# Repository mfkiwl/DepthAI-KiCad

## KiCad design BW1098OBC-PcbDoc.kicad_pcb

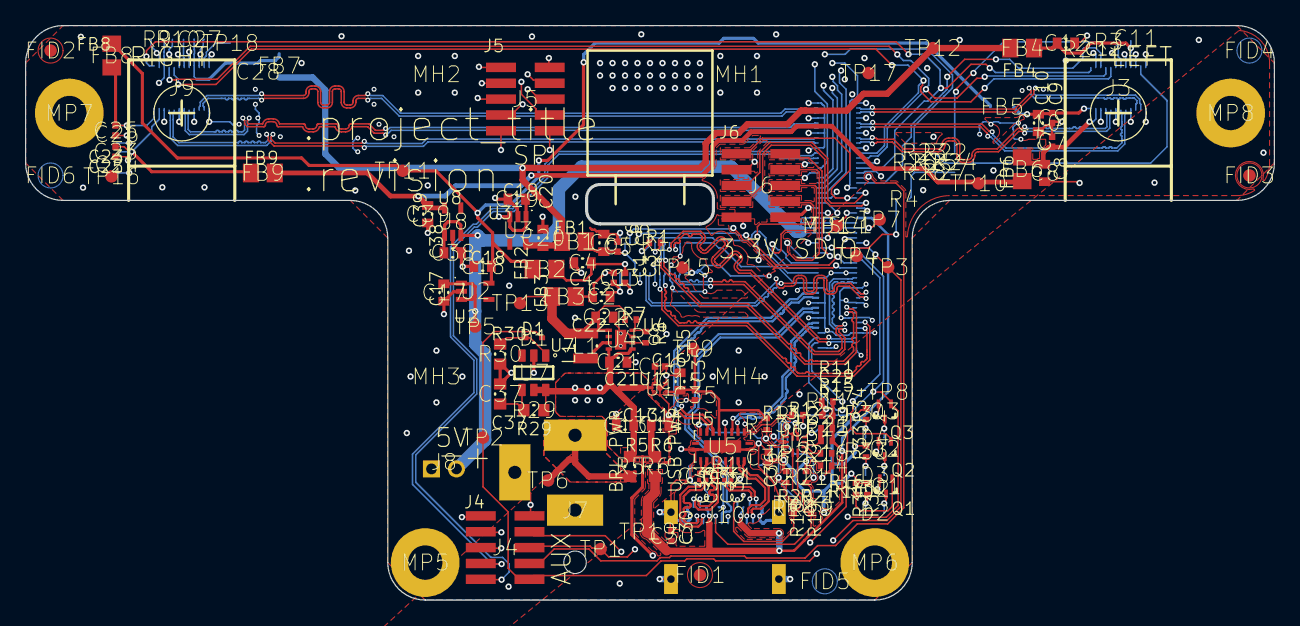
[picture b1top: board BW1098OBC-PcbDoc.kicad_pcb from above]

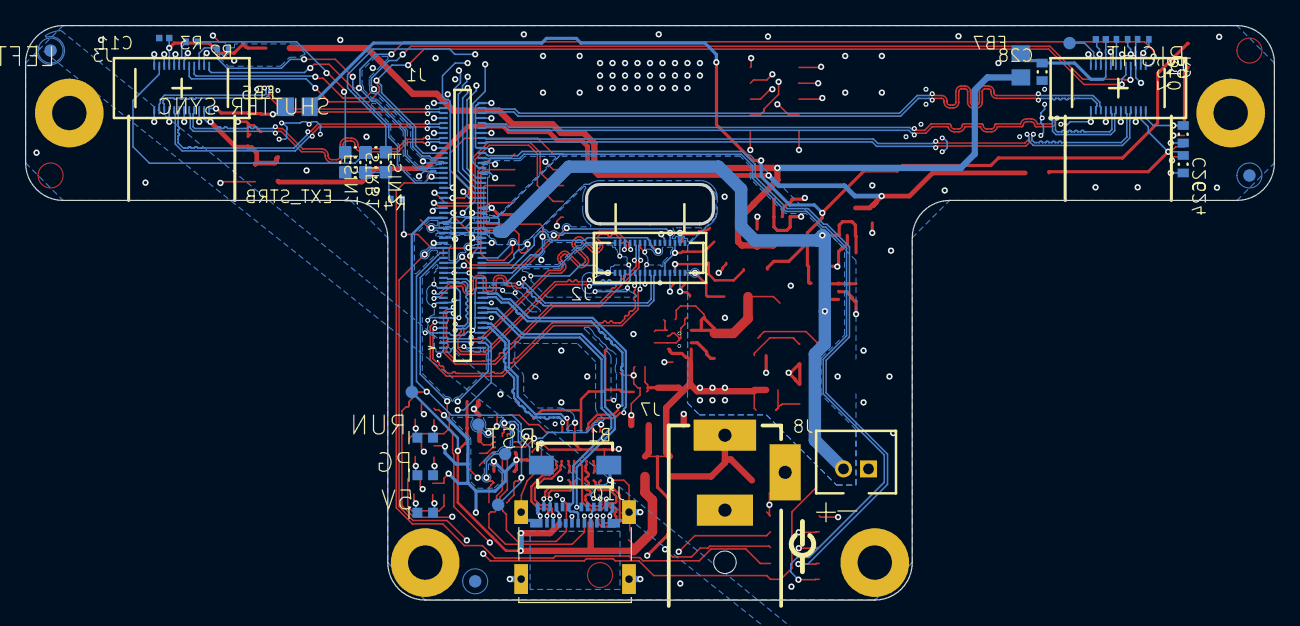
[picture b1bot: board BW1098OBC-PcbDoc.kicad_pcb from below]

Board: 4 copper layers, 100.0 x 46.0 mm, 146 parts (43 on the bottom side), 118 nets.

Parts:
B1: B1; DTSM-32N-V
C1: C1; CAPC0402(1005)70_L
C2: C2; CAPC0603(1608)100_L
C3: C3; CAPC0402(1005)70_L
C4: C4; CAPC0603(1608)100_L
C5: C5; CAPC0402(1005)70_L
C6: C6; CAPC0603(1608)100_L
C7: C7; CAPC0402(1005)70_L
C8: C8; CAPC0603(1608)100_L
C9: C9; CAPC0402(1005)70_L
C10: C10; CAPC0603(1608)100_L
C11: C11; CAPC0402(1005)70_L
C12: C12; CAPC0603(1608)100_L
C13: C13; CAPC0603(1608)100_L
C14: C14; CAPC0603(1608)100_L
C15: C15; CAPC0603(1608)100_L
C16: C16; CAPC0402(1005)70_L
C17: C17; CAPC0603(1608)100_L
C18: C18; CAPC0603(1608)100_L
C19: C19; CAPC0603(1608)100_L
C20: C20; CAPC0603(1608)100_L
C21: C21; CAPC0603(1608)100_L
C22: C22; CAPC0603(1608)100_L
C23: C23; CAPC0402(1005)70_L
C24: C24; CAPC0603(1608)100_L
C25: C25; CAPC0402(1005)70_L
C26: C26; CAPC0603(1608)100_L
C27: C27; CAPC0402(1005)70_L
C28: C28; CAPC0603(1608)100_L
C29: C29; CAPC0402(1005)70_L
C30: C30; CAPC0402(1005)70_L
C31: C31; CAPC0201(0603)33_L
C32: C32; CAPC0201(0603)33_L
C33: C33; CAPC0201(0603)33_L
C34: C34; CAPC0201(0603)33_L
C35: C35; CAPC0402(1005)70_L
C36: C36; CAPC0402(1005)70_L
C37: C37; CAPC0603(1608)100_N
C38: C38; CAPC0603(1608)100_L
C39: C39; CAPC0603(1608)100_L
D1: D1; BAS16XV2T1G
D2: D2; SML_D1xx8W
D3: D3; SML_D1xx8W
D4: D4; SML_D1xx8W
FB1: FB1; 2508056017Y2
FB2: FB2; 2508056017Y2
FB3: FB3; 2508056017Y2
FB4: FB4; 2508056017Y2
FB5: FB5; 2508056017Y2
FB6: FB6; 2508056017Y2
FB7: FB7; 2508056017Y2
FB8: FB8; 2508056017Y2
FB9: FB9; 2508056017Y2
FID1: FID1; FIDUCIAL_ROUND_1MM
FID2: FID2; FIDUCIAL_ROUND_1MM
FID3: FID3; FIDUCIAL_ROUND_1MM
FID4: FID4; FIDUCIAL_ROUND_1MM
FID5: FID5; FIDUCIAL_ROUND_1MM
FID6: FID6; FIDUCIAL_ROUND_1MM
J1: J1; DF40HC-3.0-100DS-0.4V_minpad
J2: J2; A12N02A-201
J3: J3; TG161B-201 / AN01V32 - BOARD WRAP (7MM SETBACK) MINPADS
J4: J4; 20021121-00010T1LF
J5: J5; 20021121-00010T1LF
J6: J6; 20021121-00010T1LF
J7: J7; PJ-050AH/NEB21R_COMBO
J8: J8; B2B-PH-K-S(LF)(SN)
J9: J9; TG161B-201 / AN01V32 - BOARD WRAP (7MM SETBACK) MINPADS
J10: J10; 105450-0101
L1: L1; DFE252012P-1R0M=P2
MH1: MH1; 9774030243R
MH2: MH2; 9774030243R
MH3: MH3; 9774030243R
MH4: MH4; 9774030243R
MISC1: MISC1; BW1099_Footprint
MP5: MP5; MOUNTING_HOLE_M2.5
MP6: MP6; MOUNTING_HOLE_M2.5
MP7: MP7; MOUNTING_HOLE_M2.5
MP8: MP8; MOUNTING_HOLE_M2.5
Q1: Q1; RE1C002UNTCL
Q2: Q2; RE1C002UNTCL
Q3: Q3; RE1C002UNTCL
R1: R1; RESC0402(1005)_L
R2: R2; RESC0402(1005)_L
R3: R3; RESC0402(1005)_L
R4: R4; RESC0402(1005)_L
R5: R5; RESC0603(1608)_N
R6: R6; RESC0603(1608)_N
R7: R7; RESC0402(1005)_L
R8: R8; RESC0402(1005)_L
R9: R9; RESC0402(1005)_L
R10: R10; RESC0402(1005)_L
R11: R11; RESC0402(1005)_L
R12: R12; RESC0402(1005)_L
R13: R13; RESC0402(1005)_L
R14: R14; RESC0402(1005)_L
R15: R15; RESC0402(1005)_L
R16: R16; RESC0402(1005)_L
R17: R17; RESC0402(1005)_L
R18: R18; RESC0402(1005)_L
R19: R19; RESC0402(1005)_L
R20: R20; RESC0402(1005)_L
R21: R21; RESC0402(1005)_L
R22: R22; RESC0603(1608)_N
R23: R23; RESC0603(1608)_N
R24: R24; RESC0603(1608)_N
R25: R25; RESC0603(1608)_N
R26: R26; RESC0603(1608)_N
R27: R27; RESC0603(1608)_N
R28: R28; RESC0603(1608)_N
R29: R29; RESC0603(1608)_N
R30: R30; RESC0603(1608)_N
R31: R31; RESC0402(1005)_L
R32: R32; RESC0402(1005)_L
R33: R33; RESC0402(1005)_L
R34: R34; RESC0402(1005)_L
TP1: TP1; TP100_200_NS
TP2: TP2; TP100_200_NS
TP3: TP3; TP100_200_NS
TP4: TP4; TP100_200_NS
TP5: TP5; TP100_200_NS
TP6: TP6; TP100_200_NS
TP7: TP7; TP100_200_NS
TP8: TP8; TP100_200_NS
TP9: TP9; TP100_200_NS
TP10: TP10; TP100_200_NS
TP11: TP11; TP100_200_NS
TP12: TP12; TP100_200_NS
TP13: TP13; TP100_200_NS
TP14: TP14; TP100_200_NS
TP15: TP15; TP100_200_NS
TP16: TP16; TP100_200_NS
TP17: TP17; TP100_200_NS
TP18: TP18; TP100_200_NS
TP19: TP19; TP100_200_NS
TP21: TP21; TP100_200_NS
TP22: TP22; TP100_200_NS
TP23: TP23; TP100_200_NS
U1: U1; TLV70733PDQN
U2: U2; TLV70018DCK
U3: U3; TLV70028DCK
U4: U4; TLV62080DSG
U5: U5; HD3SS3212RKSR
U6: U6; TUSB321RWBR
U7: U7; PMS150C-U06
U8: U8; TLV70012DCK

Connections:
1V2: C39.2, FB6.1, FB9.1, TP10.1, U8.5
1V2_L: C7.2, C8.2, FB6.2, J3.2
1V2_R: C23.2, C24.2, FB9.2, J9.2
1V05: C22.2, FB3.1, L1.2, R7.2, TP13.1, U4.5
1V05_IMX378: C1.2, C2.2, FB3.2, J2.15
1V8: C18.2, FB2.1, FB5.1, FB8.1, TP11.1, U2.5
1V8_IMX378: C3.2, C4.2, FB2.2, J2.13
1V8_L: C9.2, C10.2, FB5.2, J3.1
1V8_R: C25.2, C26.2, FB8.2, J9.1
2V8: C20.2, FB1.1, FB4.1, FB7.1, TP12.1, U3.5
2V8_IMX378: C5.2, C6.2, FB1.2, J2.11, J2.18
2V8_L: C11.2, C12.2, FB4.2, J3.16
2V8_R: C27.2, C28.2, FB7.2, J9.16
3V3: C15.2, C35.2, R13.2, TP9.1, U1.1, U5.6
2485_PGOOD: J1.37, J4.5, Q2.1, TP1.1
2485_WAKEUP: J1.41, J4.7, TP3.1
AUX_IO_IRQ: J1.69, J4.3
CAM_A_CLK_OUT: J1.28, J2.30
CAM_A_PWDN_N: J1.34, J2.23, R1.1
CAM_B_CLK_OUT: J1.73, J3.24, J9.24
CAM_B_D_PWM: J1.65, J9.22, R9.1
CAM_B_PWDN_N: J1.67, J3.22, R2.1
CC1: J10.A5, R18.2, U6.1
CC2: J10.B5, R19.2, U6.2
COM_AUX_IO2: J1.42, R4.1, TP4.1
FSIN1: R3.2, R22.1, R24.2
FSIN1_IN: J3.18, R3.1
FSIN2: R10.2, R23.2, R26.2
FSIN2_IN: J9.18, R10.1
GND: B1.1, C1.1, C2.1, C3.1, C4.1, C5.1, C6.1, C7.1, C8.1, C9.1, C10.1, C11.1, C12.1, C13.1, C14.1, C15.1, C16.1, C17.1, C18.1, C19.1, C20.1, C21.1, C22.1, C23.1, C24.1, C25.1, C26.1, C27.1, C28.1, C29.1, C30.1, C35.1, C36.1, C37.1, C38.1, C39.1, J1.1, J1.2, J1.7, J1.8, J1.13, J1.14, J1.19, J1.20, J1.25, J1.26, J1.30, J1.31, J1.43, J1.44, J1.45, J1.46, J1.55, J1.56, J1.57, J1.58, J1.71, J1.72, J1.75, J1.76, J1.81, J1.82, J1.87, J1.88, J1.93, J1.94, J1.99, J1.100, J2.1, J2.4, J2.7, J2.10, J2.12, J2.14, J2.17, J2.24, J2.29, J3.3, J3.6, J3.9, J3.12, J3.13, J3.15, J3.17, J3.19, J3.23, J4.9, J4.10, J5.3, J5.9, J5.10, J6.3, J6.9, J6.10, J7.2, J7.3, J8.P1, J9.3, J9.6, J9.9, J9.12, J9.13, J9.15, J9.17, J9.19, J9.23, J10.A1, J10.A12, J10.B1, J10.B12, J10.SH1, J10.SH2, J10.SH3, J10.SH4, MH1.1, MH2.1, MH3.1, MH4.1, MP5.1, MP6.1, MP7.1, MP8.1, Q1.2, Q2.2, Q3.2, R1.2, R2.2, R8.1, R9.2, R11.1, R12.2, R14.2, R16.2, R30.1, TP14.1, TP15.1, TP16.1, TP17.1, U1.2, U1.5, U2.2, U3.2, U4.2, U4.3, U4.9, U5.5, U5.11, U5.20, U5.21, U6.10, U7.2, U8.2
I2C1_SCL: J1.35, J2.20
I2C1_SDA: J1.33, J2.19
I2C2_SCL: J1.77, J3.21, J9.21
I2C2_SDA: J1.79, J3.20, J9.20
I2C3_SCL: J1.78, J4.2
I2C3_SDA: J1.80, J4.4
MIPI_RX2_C_N: J1.95, J3.11
MIPI_RX2_C_P: J1.97, J3.10
MIPI_RX2_D0_N: J1.89, J3.8
MIPI_RX2_D0_P: J1.91, J3.7
MIPI_RX2_D1_N: J1.83, J3.5
MIPI_RX2_D1_P: J1.85, J3.4
MIPI_RX3_C_N: J1.96, J9.11
MIPI_RX3_C_P: J1.98, J9.10
MIPI_RX3_D0_N: J1.90, J9.8
MIPI_RX3_D0_P: J1.92, J9.7
MIPI_RX3_D1_N: J1.84, J9.5
MIPI_RX3_D1_P: J1.86, J9.4
MIPI_RX4_C_N: J1.3, J2.28
MIPI_RX4_C_P: J1.5, J2.27
MIPI_RX4_D0_N: J1.9, J2.5
MIPI_RX4_D0_P: J1.11, J2.6
MIPI_RX4_D1_N: J1.15, J2.26
MIPI_RX4_D1_P: J1.17, J2.25
MIPI_RX5_D0_N: J1.21, J2.8
MIPI_RX5_D0_P: J1.23, J2.9
MIPI_RX5_D1_N: J1.27, J2.2
MIPI_RX5_D1_P: J1.29, J2.3
MODULE_nRST: B1.2, D1.2, J1.39, J4.1, Q3.1, TP2.1
NetD2_1: D2.1, Q1.3
NetD2_2: D2.2, R32.1
NetD3_1: D3.1, Q2.3
NetD3_2: D3.2, R33.1
NetD4_1: D4.1, Q3.3
NetD4_2: D4.2, R34.1
NetJ7_1: J7.1, R5.1, TP6.1
NetL1_1: L1.1, U4.7
NetQ1_1: Q1.1, R31.1
NetR4_2: R4.2, R24.1, R25.1, R26.1, R27.1, R27.2, R28.1, R28.2
NetR7_1: R7.1, R8.2, U4.4
NetR12_1: R12.1, U5.2
NetR13_1: R13.1, U5.9, U6.11
NetR18_1: R18.1, R20.1, TP23.1, U6.7
NetR19_1: R19.1, R21.1, TP22.1, U6.8
NetTP21_1: TP21.1, U6.6
RST_1: D1.1, R30.2, U7.1
RXB_N: J10.B10, U5.18
RXB_P: J10.B11, U5.19
RXC_N: J10.A10, U5.14
RXC_P: J10.A11, U5.15
SD_HST0_CD: J1.59, J6.7
SD_HST0_CLK: J1.61, J6.1
SD_HST0_CMD: J1.63, J6.5
SD_HST0_D0: J1.40, J6.2
SD_HST0_D1: J1.38, J6.4
SD_HST0_D2: J1.36, J6.6
SD_HST0_D3: J1.32, J6.8
SPI_SCK: J1.74, J5.1
SPI_SIO0: J1.62, J5.2
SPI_SIO1: J1.64, J5.4
SPI_SIO2: J1.66, J5.6
SPI_SIO3: J1.68, J5.8
SPI_SS_0: J1.70, J5.5
SPI_SS_1: J1.60, J5.7
STRB2: J9.14, TP18.1
STROBE1: J3.14, R22.2, R23.1, R25.2
TXB1_N: C32.2, U5.16
TXB1_P: C31.2, U5.17
TXB_N: C32.1, J10.A3
TXB_P: C31.1, J10.A2
TXC1_N: C34.2, U5.12
TXC1_P: C33.2, U5.13
TXC_N: C34.1, J10.B3
TXC_P: C33.1, J10.B2
UART_RX: J1.4, J4.6
UART_TX: J1.6, J4.8
USB_CM: R14.1, U6.3
USB_D_N: J1.18, J10.A7, J10.B7
USB_D_P: J1.16, J10.A6, J10.B6
USB_PORT: R16.1, U6.4
USB_RX_N: J1.12, U5.4
USB_RX_P: J1.10, U5.3
USB_TX_N: J1.24, U5.8
USB_TX_P: J1.22, U5.7
VBUS: C29.2, C30.2, J1.53, J10.A4, J10.A9, J10.B4, J10.B9, R6.1, R11.2, R15.1, R17.1, TP8.1, TP19.1
VBUS_DET: R15.2, R17.2, U6.5
VDD_5V: C13.2, C14.2, C16.2, C17.2, C19.2, C21.2, C36.2, C38.2, J1.47, J1.48, J1.49, J1.50, J1.51, J1.52, J1.54, J8.P2, R5.2, R6.2, R20.2, R21.2, R29.2, R31.2, R32.2, R33.2, R34.2, TP5.1, TP7.1, U1.3, U1.4, U2.1, U2.3, U3.1, U3.3, U4.1, U4.8, U6.12, U7.5, U7.6, U8.1, U8.3
nMR: C37.2, R29.1, U7.4

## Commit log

2020-12-15 adding first files
2020-12-23 Cleaned up some duplicates, started reorganizing and putting symbols into one luxonis library so the others can be deleted, added SOM Connector footprint
2020-12-23 More deletion of corrupted or duplicate files, added footprints and associations for mounting holes and 30 pin connector
2020-12-24 fixing labeling and formatting to show proper connections for pcb layout
2020-12-24 Fixed all LEFT_OV9282 sch nets, need to find datasheet for this last connector to make fp
